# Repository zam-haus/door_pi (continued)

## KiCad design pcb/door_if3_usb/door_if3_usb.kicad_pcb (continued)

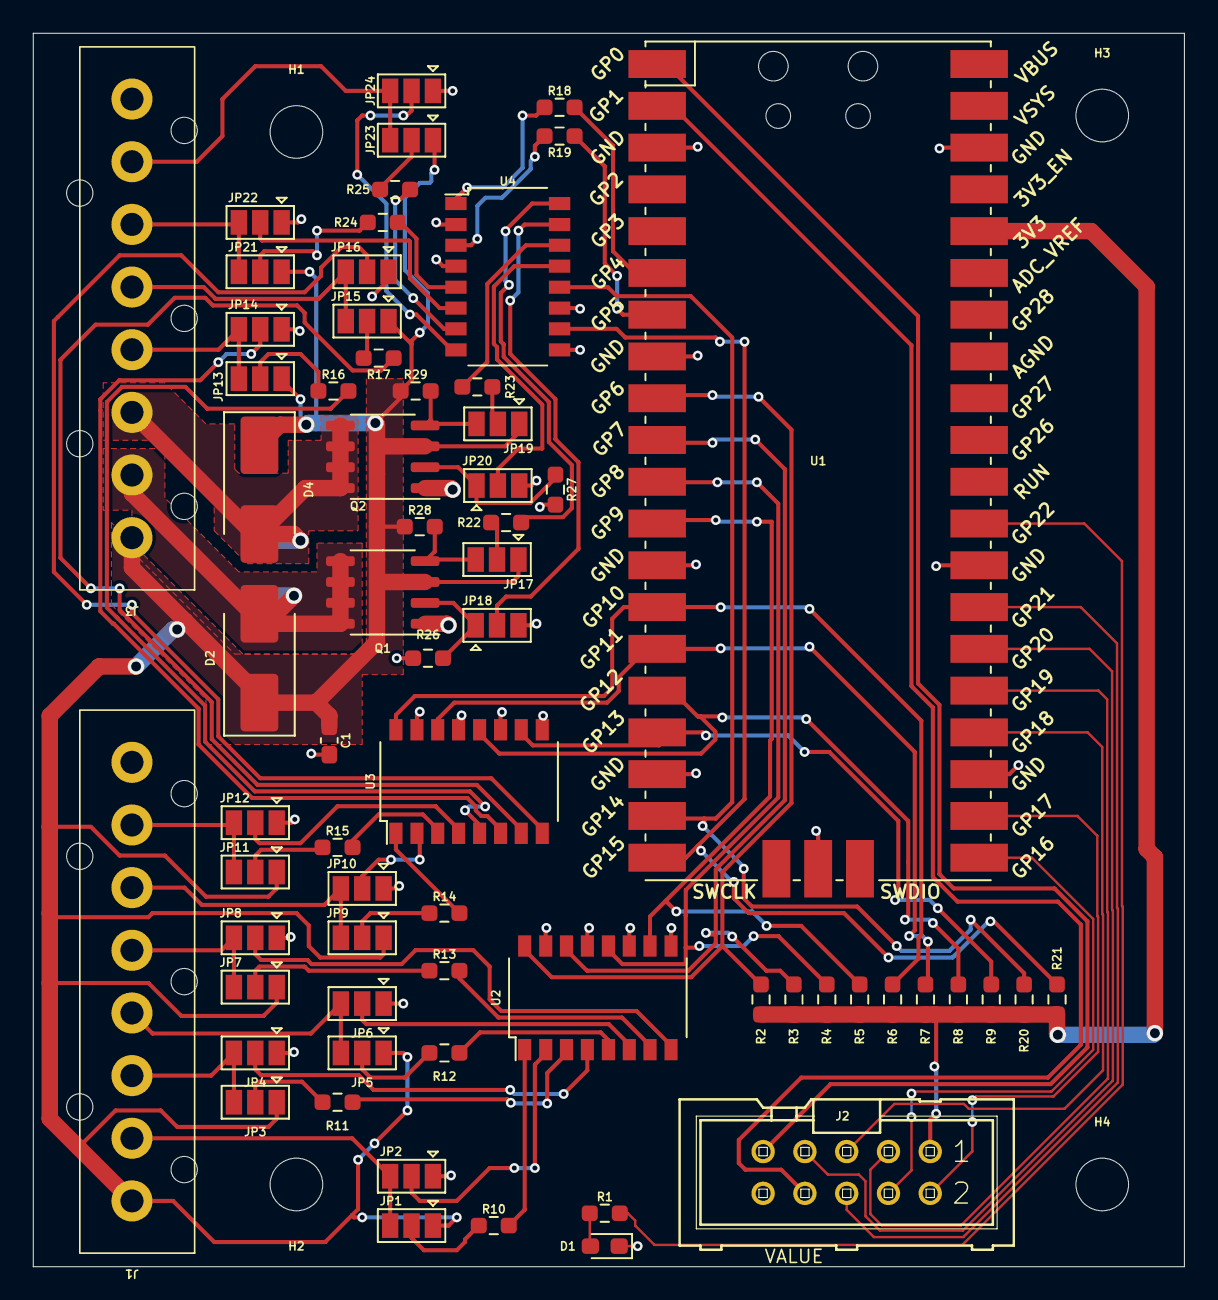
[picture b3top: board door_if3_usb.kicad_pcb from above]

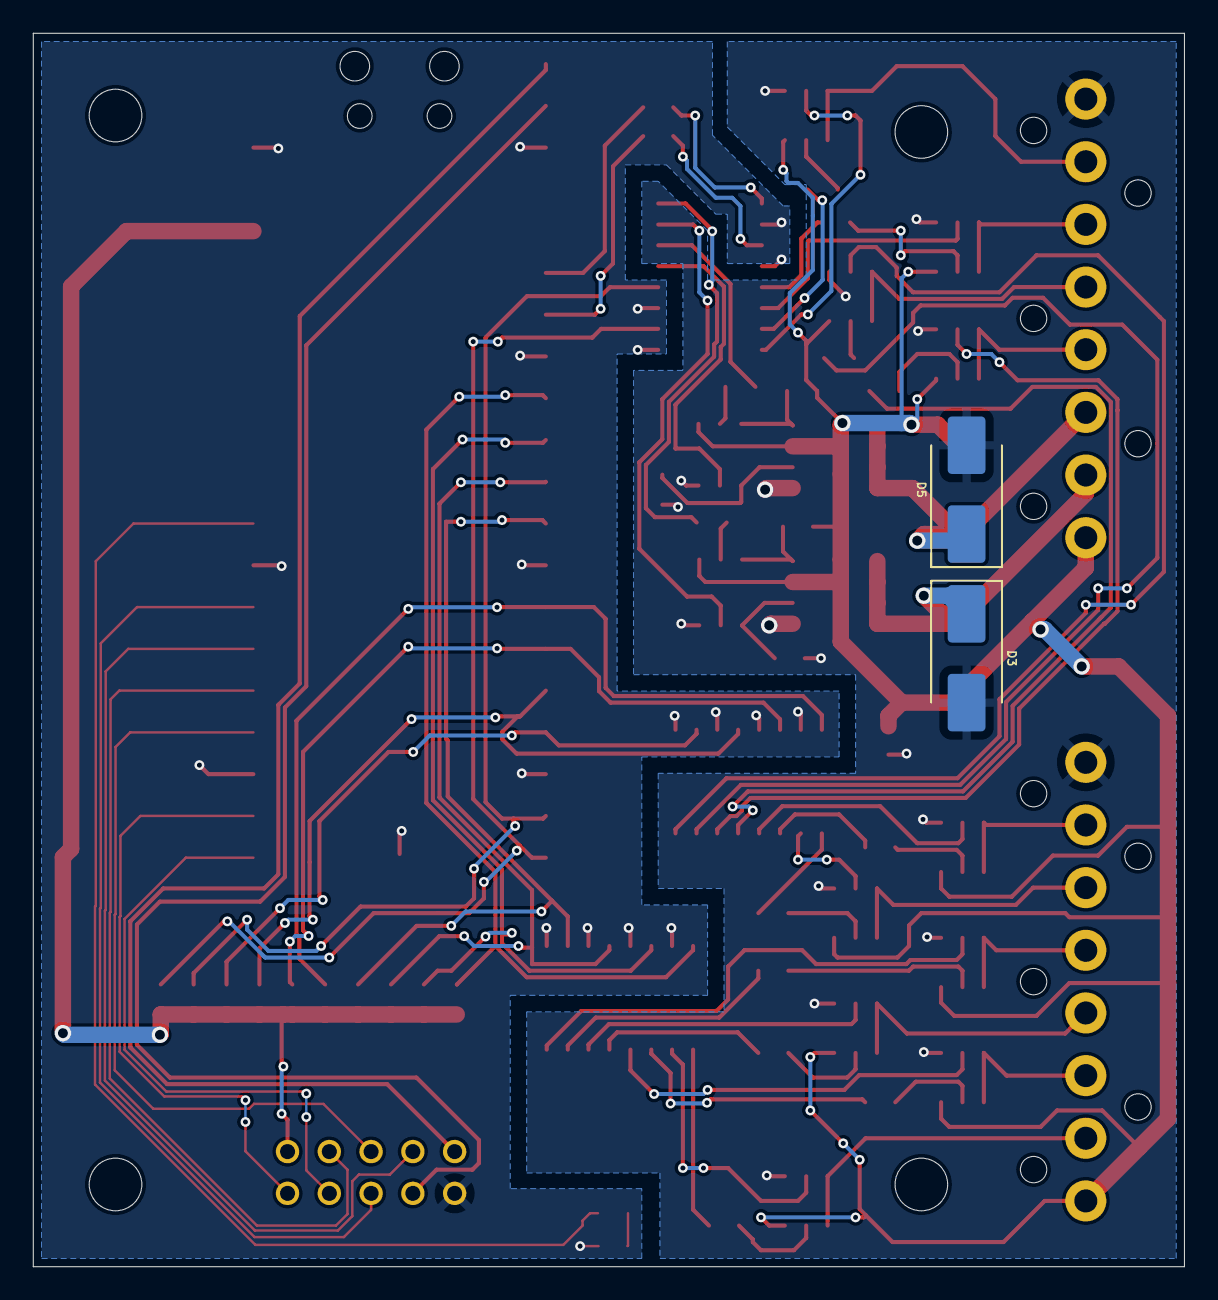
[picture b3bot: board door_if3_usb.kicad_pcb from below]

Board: 2 copper layers, 70.0 x 75.0 mm, 72 parts (2 on the bottom side), 80 nets.

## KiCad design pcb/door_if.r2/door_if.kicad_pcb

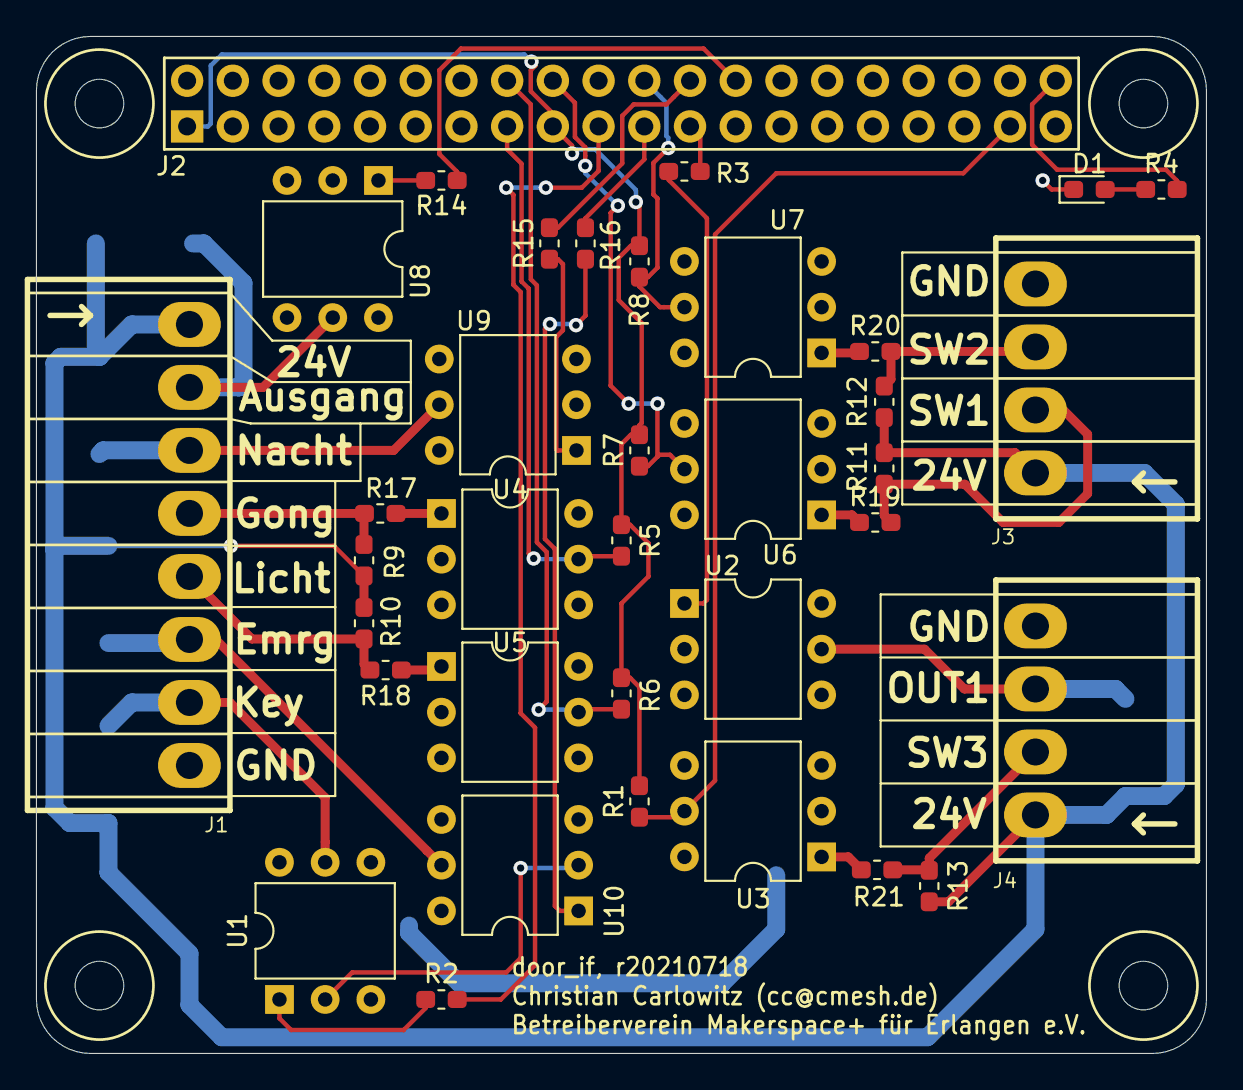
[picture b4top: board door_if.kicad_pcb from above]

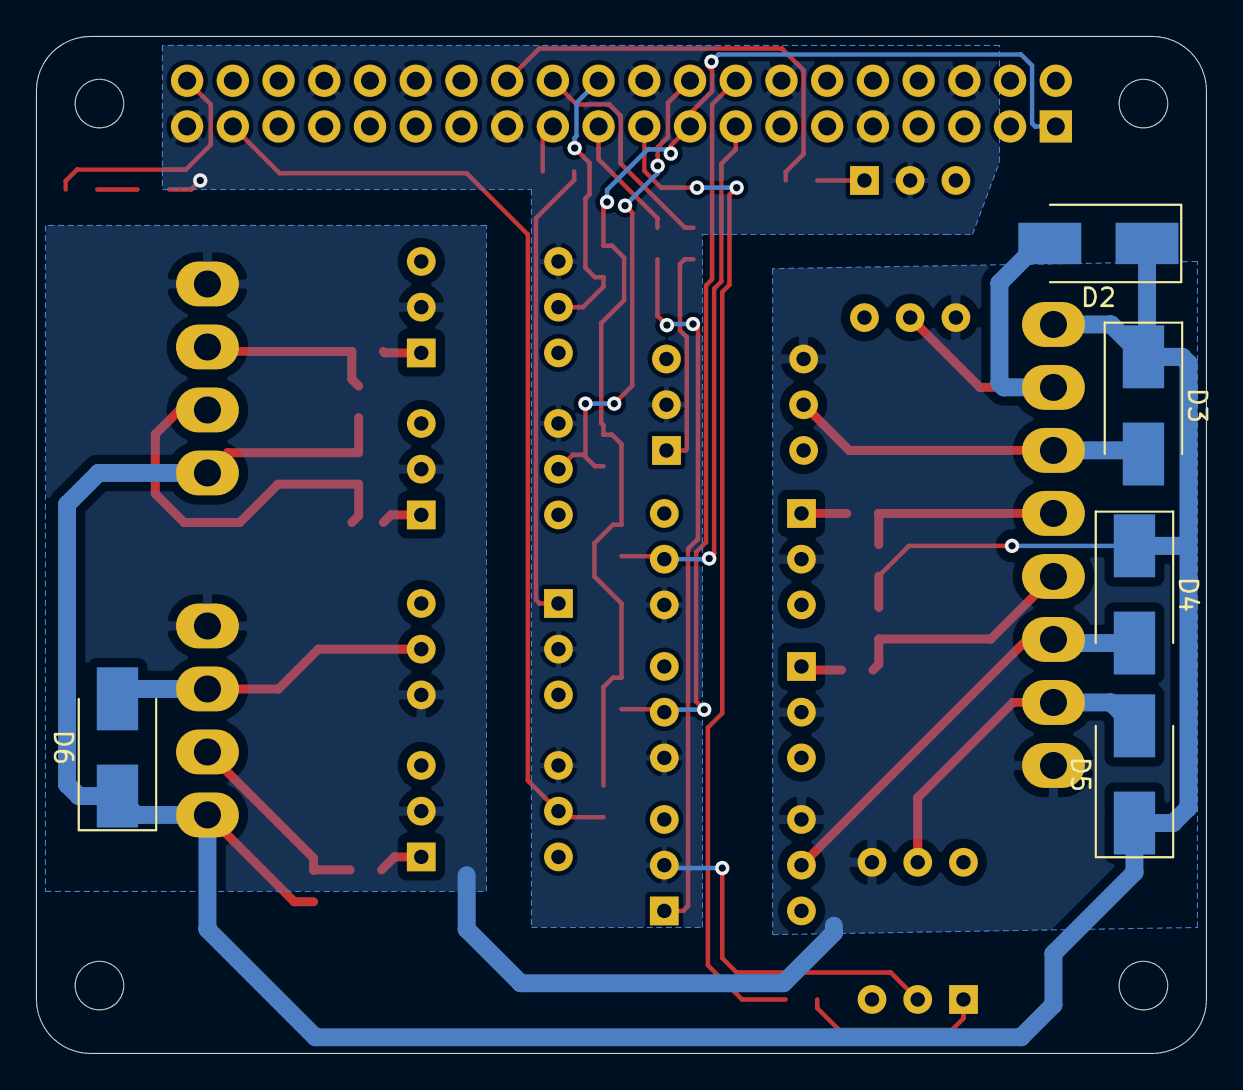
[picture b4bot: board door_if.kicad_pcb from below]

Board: 2 copper layers, 65.0 x 56.5 mm, 41 parts (5 on the bottom side), 36 nets.

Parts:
D1: LED; LED_0603_1608Metric_Pad1.05x0.95mm_HandSolder
D2, D3, D4, D5, D6: MBRS240; D_SMB_Handsoldering
J1: Conn_01x08; con-ria-TYPE_182_169_8PIN
J2: Raspberry_Pi_2_3; CC_RPI_3_4
J3, J4: Conn_01x04; con-ria-TYPE_182_169_4PIN
R1, R5, R6, R7, R8: 10k; R_0603_1608Metric_Pad1.05x0.95mm_HandSolder
R2, R3, R14, R15, R16: 220; R_0603_1608Metric_Pad1.05x0.95mm_HandSolder
R4: 470; R_0603_1608Metric_Pad1.05x0.95mm_HandSolder
R9, R10, R11, R12, R13: 22k; R_0603_1608Metric_Pad1.05x0.95mm_HandSolder
R17, R18, R19, R20, R21: 0; R_0603_1608Metric_Pad1.05x0.95mm_HandSolder
U1, U2, U3, U4, U5, U6, U7, U8, U9, U10: 4N32; DIP-6_W7.62mm

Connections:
+3V3: J2.1, J2.17, R1.2, R5.2, R6.2, R7.2, R8.2
+24V: D2.1, D3.1, D4.1, D5.1, D6.1, J1.1, J3.1, J4.1, R9.2, R10.2, R11.2, R12.2, R13.2
Ausgang: D2.2, J1.2, U8.5
Emergency: D4.2, J1.6, U10.5
GND: D1.1, J2.6, J2.9, J2.14, J2.20, J2.25, J2.30, J2.34, J2.39, U1.2, U2.2, U3.4, U4.4, U5.4, U6.4, U7.4, U8.2, U9.2, U10.2
GNDA: J1.8, J3.4, J4.4, U1.4, U2.4, U3.2, U4.2, U5.2, U6.2, U7.2, U8.4, U9.4, U10.4
Gong: J1.4, R9.1, R17.2
I_Gong: J2.15, R5.1, U4.5
I_Licht: J2.16, R6.1, U5.5
I_SW1: J2.18, R7.1, U6.5
I_SW2: J2.22, R8.1, U7.5
I_SW3: J2.37, R1.1, U3.5
Key: D5.2, J1.7, U1.5
Licht: J1.5, R10.1, R18.2
Nacht: D3.2, J1.3, U9.5
unnamed: D1.2, R4.1
unnamed: R2.1, U1.1
unnamed: R3.1, U2.1
unnamed: R14.1, U8.1
unnamed: R15.1, U9.1
unnamed: R16.1, U10.1
unnamed: R17.1, U4.1
unnamed: R18.1, U5.1
unnamed: R19.1, U6.1
unnamed: R20.1, U7.1
unnamed: R21.1, U3.1
OUT1: D6.2, J4.3, U2.5
O_Ausgang: J2.26, R14.2
O_Emergency: J2.21, R16.2
O_Key: J2.19, R2.2
O_LED: J2.40, R4.2
O_Nacht: J2.24, R15.2
O_Out1: J2.23, R3.2
SW1: J3.2, R11.1, R19.2
SW2: J3.3, R12.1, R20.2
SW3: J4.2, R13.1, R21.2

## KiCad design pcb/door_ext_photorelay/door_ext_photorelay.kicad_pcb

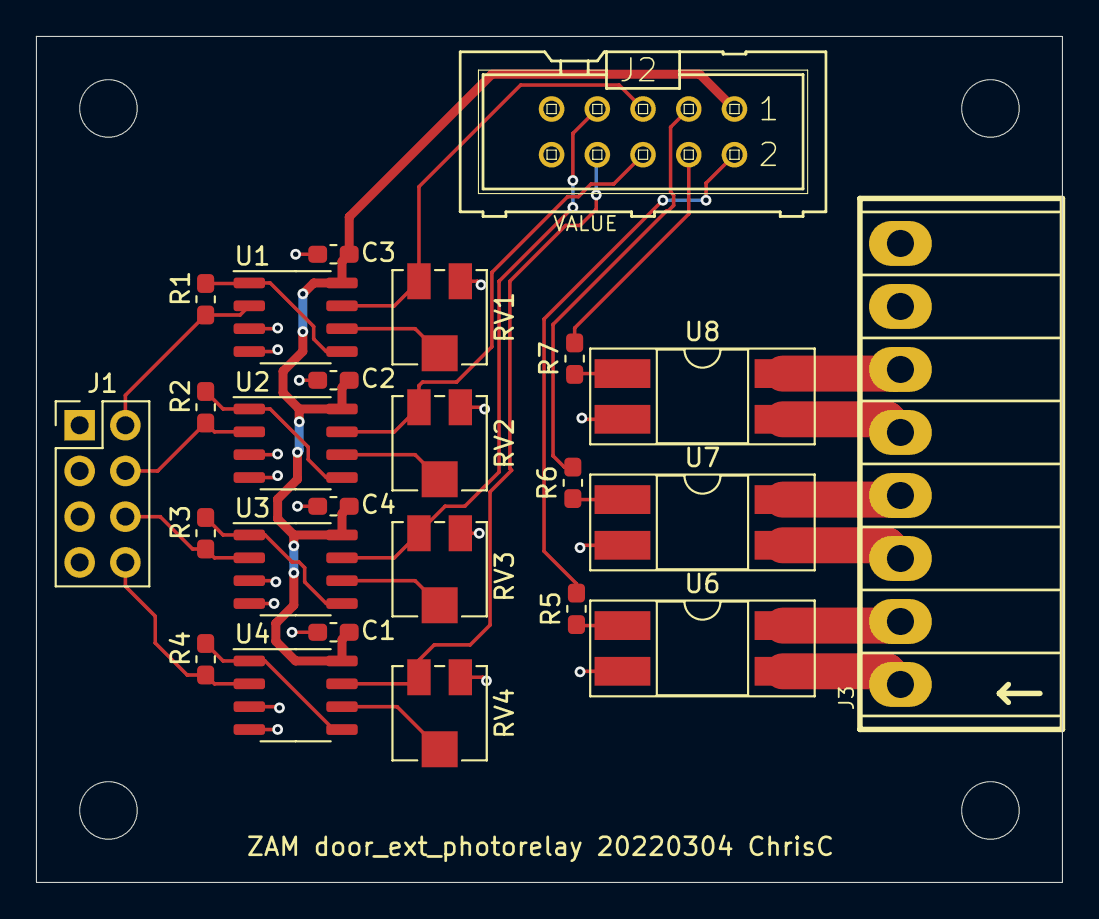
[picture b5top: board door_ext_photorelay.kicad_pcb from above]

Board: 2 copper layers, 57.0 x 47.0 mm, 29 parts (0 on the bottom side), 30 nets.

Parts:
C1, C2, C3, C4: 100n; C_0603_1608Metric_Pad1.05x0.95mm_HandSolder
H1, H2, H3, H4: MountingHole; MountingHole_3.2mm_M3
J1: Conn_02x04_Odd_Even; PinHeader_2x04_P2.54mm_Vertical
J2: Conn_02x05_Odd_Even; con-harting-ml-ML10
J3: Conn_01x08; con-ria-TYPE_182_169_8PIN
R1, R2, R3, R4, R5, R6, R7: R; R_0603_1608Metric_Pad1.05x0.95mm_HandSolder
RV1, RV2, RV3, RV4: R_POT; Potentiometer_Vishay_TS53YJ_Vertical
U1, U2, U3, U4: TS912; SO-8_3.9x4.9mm_P1.27mm
U6, U7, U8: TLP3555A; DIP-4_W8.89mm_SMDSocket_LongPads

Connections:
+3V3: C1.1, C2.1, C3.1, C4.1, J2.1, U1.8, U2.8, U3.8, U4.8
/PD0: J1.2, R1.2, U1.2
/PD1: J1.4, R2.2, U2.2
/PD2: J1.6, R3.2, U3.2
/PD3: J1.8, R4.2, U4.2
GND: C1.2, C2.2, C3.2, C4.2, J1.1, J1.3, J1.5, J1.7, J2.10, RV1.3, RV2.3, RV3.3, RV4.3, U1.3, U1.4, U2.3, U2.4, U3.3, U3.4, U4.3, U4.4, U6.2, U7.2, U8.2
GPIO0: J2.2, R5.2
GPIO1: J2.3, R6.2
GPIO2: J2.4, R7.2
GPIO3: J2.5, RV1.1, U1.7
GPIO4: J2.6, RV2.1, U2.7
GPIO5: J2.7, RV3.1, U3.7
GPIO6: J2.8, RV4.1, U4.7
unnamed: J3.1, U6.3
unnamed: J3.2, U6.4
unnamed: J3.3, U7.3
unnamed: J3.4, U7.4
unnamed: J3.5, U8.3
unnamed: J3.6, U8.4
unnamed: R1.1, U1.1, U1.5
unnamed: R2.1, U2.1, U2.5
unnamed: R3.1, U3.1, U3.5
unnamed: R4.1, U4.1, U4.5
unnamed: R5.1, U6.1
unnamed: R6.1, U7.1
unnamed: R7.1, U8.1
unnamed: RV1.2, U1.6
unnamed: RV2.2, U2.6
unnamed: RV3.2, U3.6
unnamed: RV4.2, U4.6

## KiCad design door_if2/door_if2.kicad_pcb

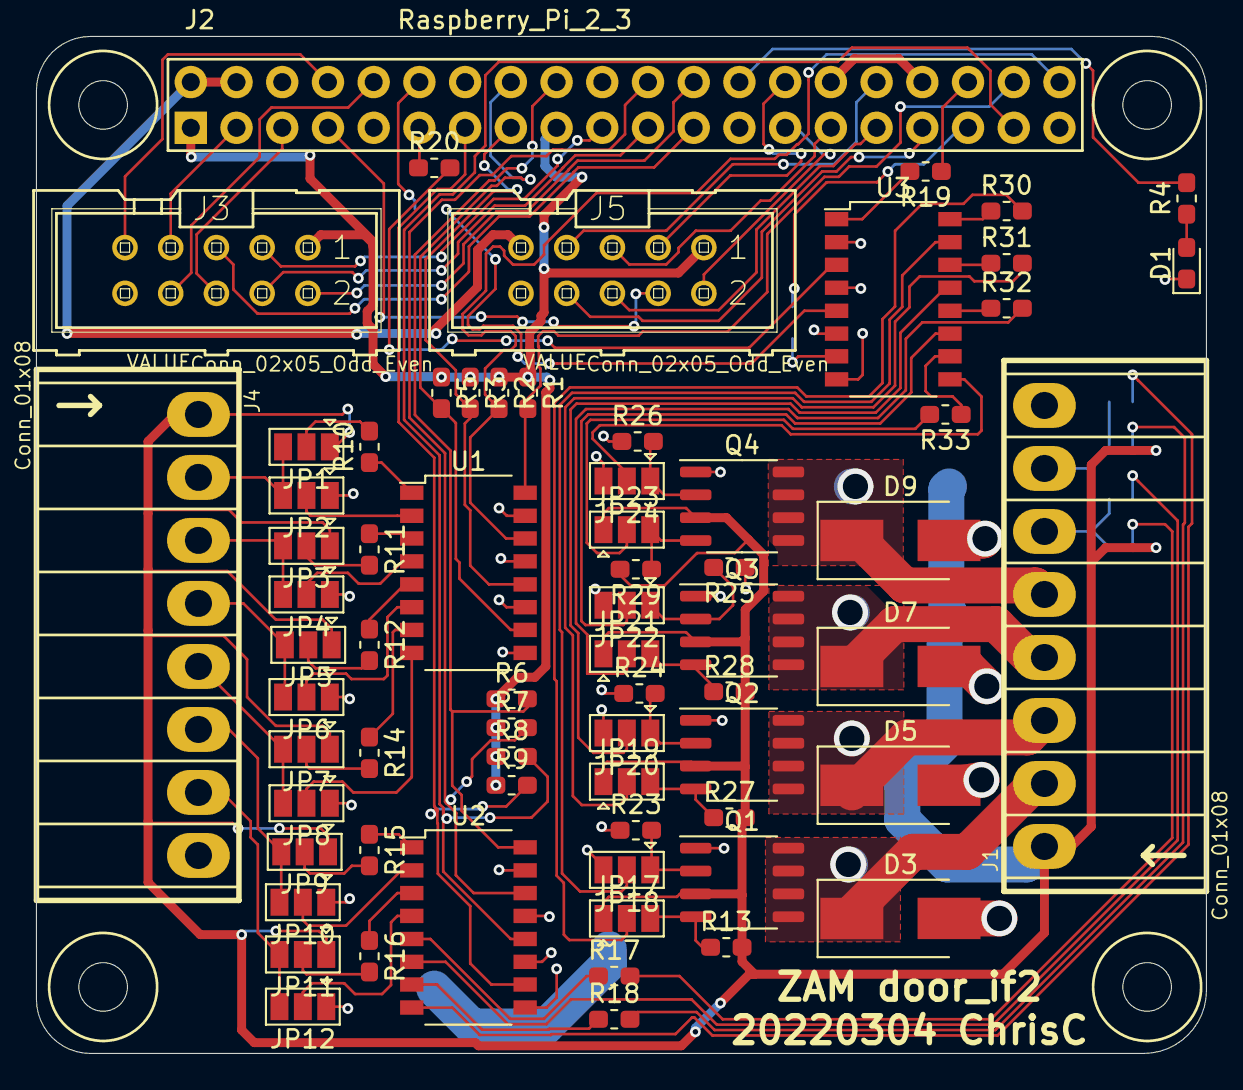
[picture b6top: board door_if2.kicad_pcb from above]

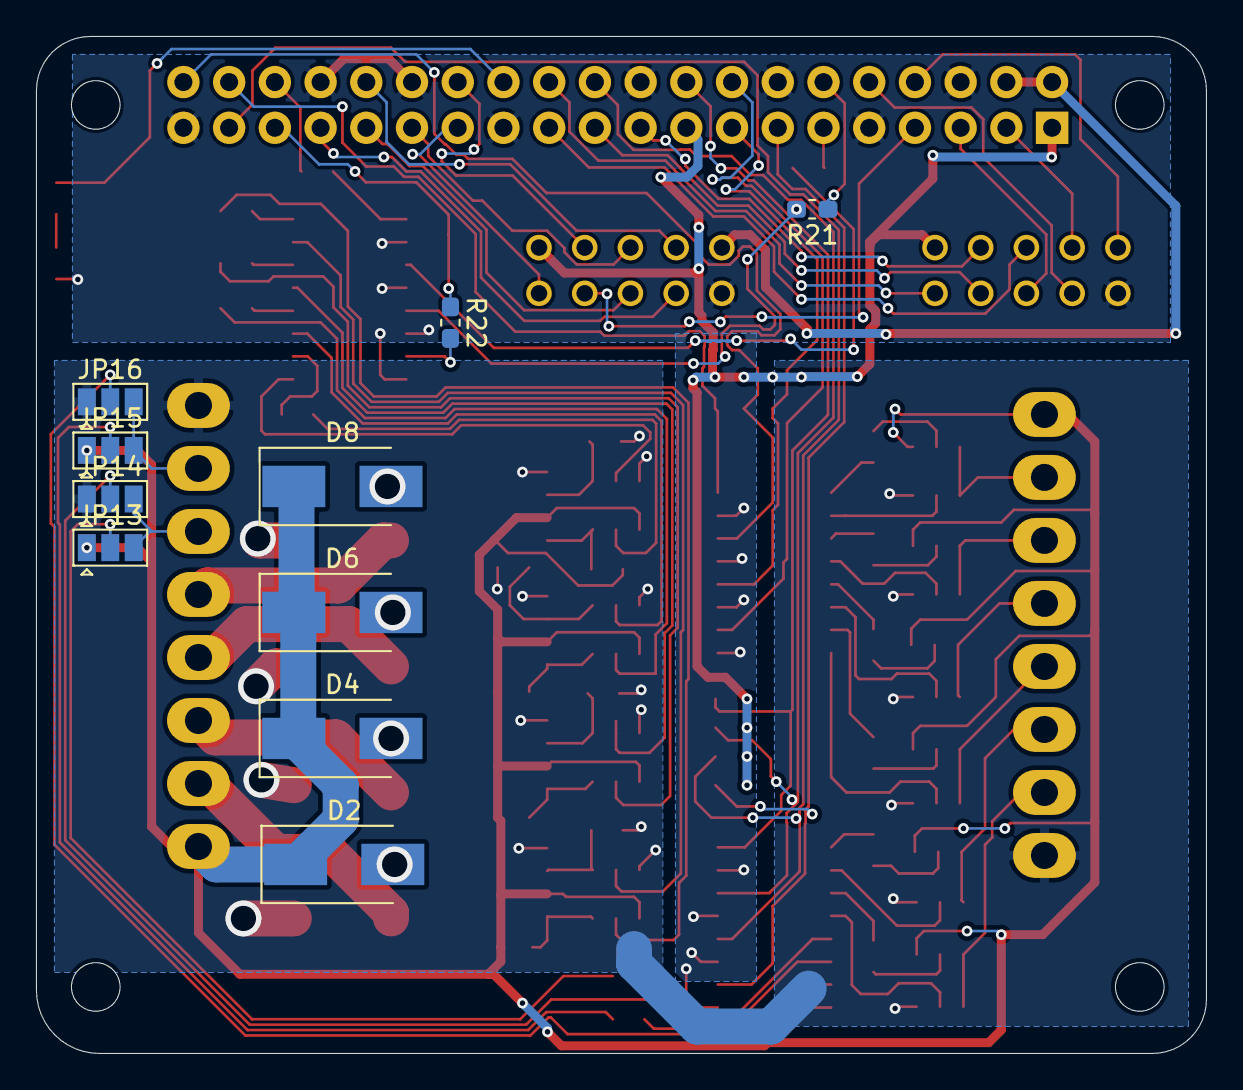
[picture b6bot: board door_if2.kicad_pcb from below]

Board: 2 copper layers, 65.0 x 56.5 mm, 78 parts (10 on the bottom side), 94 nets.

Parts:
D1: LED; LED_0603_1608Metric_Pad1.05x0.95mm_HandSolder
D2, D3, D4, D5, D6, D7, D8, D9: MBRS240; D_SMB_Handsoldering
J1, J4: Conn_01x08; con-ria-TYPE_182_169_8PIN
J2: Raspberry_Pi_2_3; CC_RPI_3_4
J3, J5: Conn_02x05_Odd_Even; con-harting-ml-ML10
JP1, JP2, JP3, JP4, JP5, JP6, JP7, JP8, JP9, JP10, JP11, JP12, JP13, JP14, JP15, JP16, JP17, JP18, JP19, JP20, JP21, JP22, JP23, JP24: SolderJumper_3_Open; SolderJumper-3_P1.3mm_Open_Pad1.0x1.5mm
Q1, Q2, Q3, Q4: IRF7343; SO-8_3.9x4.9mm_P1.27mm
R1, R2, R3, R5, R6, R7, R8, R9, R13, R23, R24, R25, R26, R27, R28, R29, R30, R31, R32, R33: 10k; R_0603_1608Metric_Pad1.05x0.95mm_HandSolder
R4: 470; R_0603_1608Metric_Pad1.05x0.95mm_HandSolder
R10, R11, R12, R14, R15, R16, R17, R18: 1k; R_0603_1608Metric_Pad1.05x0.95mm_HandSolder
R19, R20, R21, R22: 220; R_0603_1608Metric_Pad1.05x0.95mm_HandSolder
U1, U2, U3: LTV-247; SOP-16_4.4x10.4mm_P1.27mm

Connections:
+3V3: J2.1, J2.17, J3.1, J5.1, R1.1, R2.1, R3.1, R5.1, R6.1, R7.1, R8.1, R9.1
+5V: J2.2, J2.4, J5.9
+12V: D2.1, D4.1, D6.1, D8.1, J1.1, J4.1, JP1.1, JP3.1, JP5.1, JP7.1, JP9.1, JP11.1, JP13.1, JP15.1, JP17.1, JP19.1, JP21.1, JP23.1, Q1.3, Q2.3, Q3.3, Q4.3, R13.2, R27.2, R28.2, R29.2
GND: D1.1, J2.6, J2.9, J2.14, J2.20, J2.25, J2.30, J2.34, J2.39, J3.10, J5.10, U1.9, U1.11, U1.13, U1.15, U2.9, U2.11, U2.13, U2.15, U3.2, U3.4, U3.6, U3.8
GNDA: D3.2, D5.2, D7.2, D9.2, J1.8, J4.8, JP2.1, JP4.1, JP6.1, JP8.1, JP10.1, JP12.1, JP14.1, JP16.1, JP18.3, JP20.3, JP22.3, JP24.3, Q1.1, Q2.1, Q3.1, Q4.1, R23.1, R24.1, R25.1, R26.1
GPIO0: J2.27, J5.2
GPIO1: J2.28, J5.3
GPIO2: J2.7, J5.4
GPIO3: J2.29, J5.5
GPIO4: J2.31, J5.6
GPIO5: J2.32, J5.7
GPIO6: J2.33, J5.8
I2C_SCL: J2.5, J3.6
I2C_SDA: J2.3, J3.7
IN1: J4.2, JP1.3, JP2.3
IN2: J4.3, JP3.3, JP4.3
IN3: J4.4, JP5.3, JP6.3
IN4: J4.5, JP7.3, JP8.3
IN5: J4.6, JP9.3, JP10.3
IN6: J4.7, JP11.3, JP12.3
IN7: J1.6, JP13.3, JP14.3
IN8: J1.7, JP15.3, JP16.3
unnamed: D1.2, R4.1
unnamed: JP1.2, R10.2
unnamed: JP2.2, U1.2
unnamed: JP3.2, R11.2
unnamed: JP4.2, U1.4
unnamed: JP5.2, R12.2
unnamed: JP6.2, U1.6
unnamed: JP7.2, R14.2
unnamed: JP8.2, U1.8
unnamed: JP9.2, R15.2
unnamed: JP10.2, U2.2
unnamed: JP11.2, R16.2
unnamed: JP12.2, U2.4
unnamed: JP13.2, R17.2
unnamed: JP14.2, U2.6
unnamed: JP15.2, R18.2
unnamed: JP16.2, U2.8
unnamed: JP17.2, R30.2
unnamed: JP17.3, Q1.4, R13.1
unnamed: JP18.1, Q1.2, R23.2
unnamed: JP18.2, U3.15
unnamed: JP19.2, R31.2
unnamed: JP19.3, Q2.4, R27.1
unnamed: JP20.1, Q2.2, R24.2
unnamed: JP20.2, U3.13
unnamed: JP21.2, R32.2
unnamed: JP21.3, Q3.4, R28.1
unnamed: JP22.1, Q3.2, R25.2
unnamed: JP22.2, U3.11
unnamed: JP23.2, R33.2
unnamed: JP23.3, Q4.4, R29.1
unnamed: JP24.1, Q4.2, R26.2
unnamed: JP24.2, U3.9
unnamed: R10.1, U1.1
unnamed: R11.1, U1.3
unnamed: R12.1, U1.5
unnamed: R14.1, U1.7
unnamed: R15.1, U2.1
unnamed: R16.1, U2.3
unnamed: R17.1, U2.5
unnamed: R18.1, U2.7
unnamed: R19.2, U3.1
unnamed: R20.2, U3.3
unnamed: R21.2, U3.5
unnamed: R22.2, U3.7
unnamed: R30.1, U3.16
unnamed: R31.1, U3.14
unnamed: R32.1, U3.12
unnamed: R33.1, U3.10
OUT1: D2.2, D3.1, J1.2, Q1.5, Q1.6, Q1.7, Q1.8
OUT2: D4.2, D5.1, J1.3, Q2.5, Q2.6, Q2.7, Q2.8
OUT3: D6.2, D7.1, J1.4, Q3.5, Q3.6, Q3.7, Q3.8
OUT4: D8.2, D9.1, J1.5, Q4.5, Q4.6, Q4.7, Q4.8
O_LED: J2.26, R4.2
SPI_CLK: J2.23, J3.5
SPI_CS: J2.24, J3.2
SPI_MISO: J2.21, J3.4
SPI_MOSI: J2.19, J3.3
S_IN1: J2.38, R1.2, U1.16
S_IN2: J2.40, R2.2, U1.14
S_IN3: J2.15, R3.2, U1.12
S_IN4: J2.16, R5.2, U1.10
S_IN5: J2.18, R6.2, U2.16
S_IN6: J2.22, R7.2, U2.14
S_IN7: J2.37, R8.2, U2.12
S_IN8: J2.13, R9.2, U2.10
S_OUT1: J2.36, R19.1
S_OUT2: J2.11, R20.1
S_OUT3: J2.12, R21.1
S_OUT4: J2.35, R22.1
UART_RX: J2.10, J3.8
UART_TX: J2.8, J3.9

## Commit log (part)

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2021-08-26 added PCB design for door interface and RasPi setup instructions
2021-08-27 added instruction to disable dphys-swap
2021-08-27 added basic door manager HAL
2021-09-01 added very simple HAL simulation mode and callback test
2021-09-02 added term signal on Ctrl+D in door_hal
2021-09-02 added simple door_manager mqtt interface
2021-09-03 add logging and fix docopt requirement
2021-09-03 fixed env, explicity stop mqtt loop
2021-09-03 migrated to pipenv
2021-09-03 cleanup gpio thread
2021-09-03 load mqtt connection dicts directly from config
2021-09-03 added systemd service file
2021-09-03 ignore door_manager/config.json in git
2021-09-03 added raspi setup instructions for door_manager
2021-09-03 added setup instruction to adjust config file
2021-10-08 implemented door open on usr1 signal
2021-10-22 implemented presence indicator
2021-10-22 fixed door presence pin interpretation and json compatibility
2021-10-22 added door_if revision with open collector input driver support
2021-10-22 transmit gong on mqtt
2022-02-16 fixed error in setup doc
2022-02-26 added door_if2
2022-03-06 added boards
2022-03-24 implemented rpi image file preparation
2022-03-24 added readme instructions, created template for readonly root
2022-04-24 fixed rpi image setup
2022-04-29 implemented rpi readonly setup with ansible
2022-05-06 completed basic rpi setup with ansible
2022-05-06 implemented file-based gpio config in hal
2022-05-06 implemented file-based gpio config in hal (II)
2022-05-13 added config for door_if2 signals
2022-08-07 fixed hostname setting in ansible scripts, small bugfixes
2022-08-07 fixed connection plan
2022-08-12 moved pcbs to subfolder
2022-08-12 moved connection plans
2022-08-12 fixed door manager for new hal abstraction
2022-08-13 per-host gpio config
2022-08-19 small fixes to allow integrating front door
2022-08-19 added hosts file
2022-08-19 refactored door-manager input setup, added missing example entries for config
2022-08-19 implemented is_open status message for dormakaba locks
2022-12-09 added tmpfs for NetworkManager and logrotate
2022-12-09 ensure dhcpcd is disabled
2023-03-24 added door if pcb version 3
2023-03-27 output all input states on mqtt, fixed sim mode
2023-03-27 added missing connection plan for switch version
2023-07-05 added machine variant of if3_usb
2023-07-06 completed if3_usb_machine
2023-07-07 finalized if3_usb_machine pcb
2023-07-12 added case designs
2023-07-13 added basic uc program for micropython (rp2)
2023-07-15 fixed bug in ansible script
2023-07-15 updated ignores
2023-07-20 make log level configurable
2023-07-20 implemented basic usb hal
2023-09-03 completed usb module implementation, improved uc code with non-blocking input
2023-09-03 added relais mount
2023-09-15 fixed bug with decorator
2023-09-15 changed night command to day
2023-11-01 added door_if4 design
2023-11-03 almost completed door_if4_usb for manufacturing
2023-11-27 added final if4 design
2023-11-28 added case design for if4
2023-11-28 if4 case height fix
2023-12-15 added new if4 case
2023-12-15 increased clamp thickness in if4 case
2023-12-15 added if4 case stl
2023-12-15 added connection plans for if3
2023-12-27 added v2 of if4 board
2023-12-29 adapted uc code for if4.v2
2024-02-04 added old implementation
2024-02-04 added interactive shell to test_cli
2024-02-06 added pcb test program
2024-02-13 debug/bugfixes for new usb controller
2024-02-13 added new config variables
2024-02-13 implemented software permaopen
2024-02-23 implemented locking for serial port in door_hal, display event messages
2024-02-23 read all inputs on start
2024-02-23 reduce usb polling interval to 1s
2024-04-21 implemented svp6000 (dormakaba) functionality with usb hardware (if4.v2)
2024-07-10 Pi4 case for DIN
2024-07-10 Added original lit
2024-10-22 liegt so auf dem pi
2025-03-08 stand suedwestrueckseite
2025-03-08 add updated picopi conde and example config
2025-05-21 remove day mode, make program cycling independent of input type
2025-05-21 add "switch" mode for program change to implement the day/night switches
2025-07-30 BREAKING: door_manager sends H/L/Z instead of on/off
2025-07-30 resolve deprecation: split differenciate get_event_loop calls
2025-08-11 door_manager: move global config and functions into DoorManager to allow later config parsing
2025-08-13 fix missiong -c in commandline parsing
2025-08-13 door_manager: convert to python package. this is a step to create a debian package from it.
2025-08-13 systemd unit: add templated version running vom /usr an /etc for use with multiple doors
2025-08-13 debian package for door_manager
2025-08-25 changes required for fail-open and active low buttons
2025-08-25 door-manager: bump version to 1.1.
2025-11-14 fix version in changelog, its now 1.1.0
2026-05-25 Fix dependencies
2026-05-25 gitignore pycharm
